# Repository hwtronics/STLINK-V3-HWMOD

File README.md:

# STLINK-V3-HWMOD

Custom developed board that allow you to use the new STLINK-V3MODS with the Tag-Connect cable.

## Preview of the board:

## Prerequisite
Autodesk Eagle

## Social Media Links

Instagram: [@hwtronics](https://www.instagram.com/hwtronics/)
Facebook: [@hwtronics](https://www.facebook.com/hwtronics/)
Twitter: [@hwtronics](https://twitter.com/hwtronics)

Distributed under the GNU General Public License v3.0 license. See ``LICENSE`` for more information.

For any further info please contact us by email: info@hwtronics.com !!!

## Contributors

-[@dinamitemic](https://github.com/dinamitemic)
-[@AnnaBiguzzi](https://github.com/AnnaBiguzzi)

## Contributing

1. Fork it (<https://github.com/yourname/yourproject/fork>)
2. Create your feature branch (`git checkout -b feature/fooBar`)
3. Commit your changes (`git commit -am 'Add some fooBar'`)
4. Push to the branch (`git push origin feature/fooBar`)
5. Create a new Pull Request

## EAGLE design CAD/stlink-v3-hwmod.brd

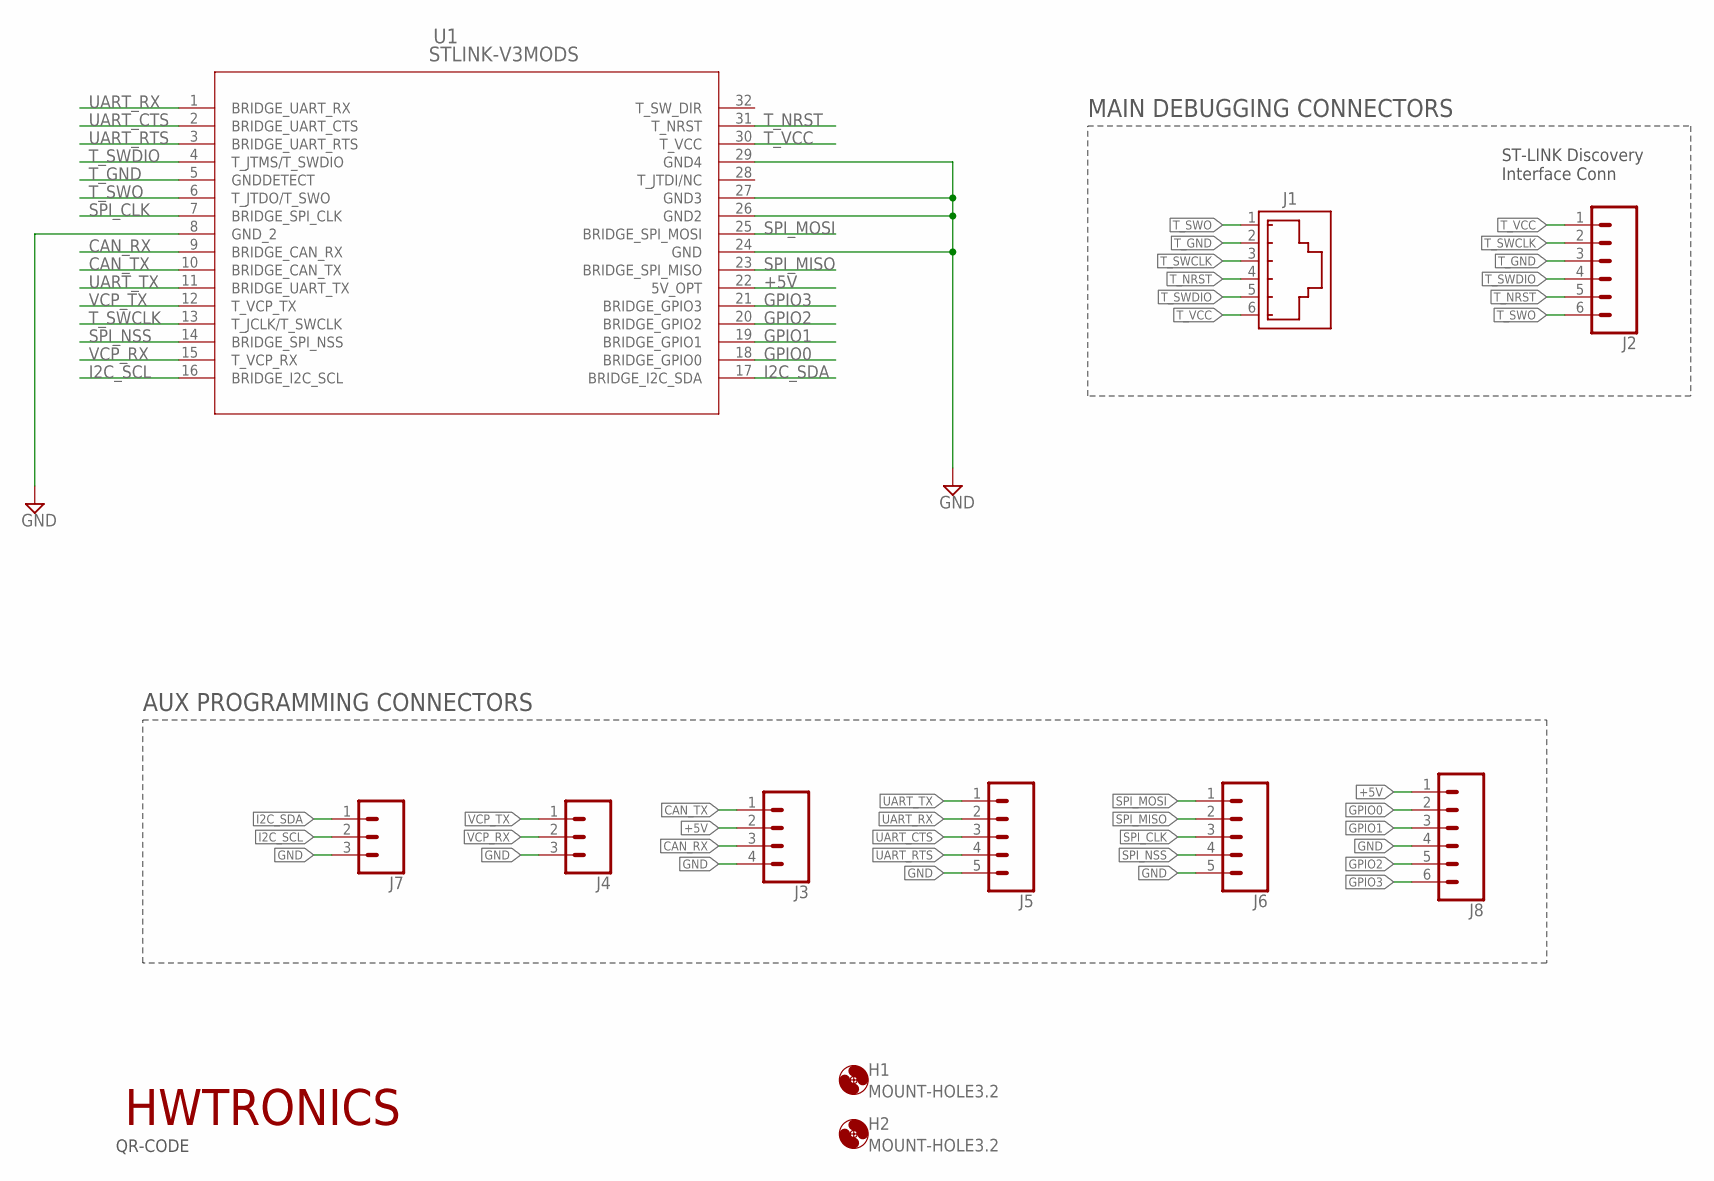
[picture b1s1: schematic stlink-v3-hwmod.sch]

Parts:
H1, H2: MOUNT-HOLE3.2; 3,2
J1: 615006143621
J2, J8: CONN_06SILK_FEMALE_PTH; 1X06
J3: CONN_04; 1X04
J4, J7: CONN_03; 1X03
J5, J6: CONN_05; 1X05
LOGO1: LOGO-HWTRONICS-10MM; HWTRONICS-10MM
U1: STLINK-V3MODS; MOD_STLINK-V3M_MB1467
U$1: STLINK-V3-HWMODS

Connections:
+5V: J3.2, J8.1, U1.22 (5V_OPT)
CAN_RX: J3.3, U1.9 (BRIDGE_CAN_RX)
CAN_TX: J3.1, U1.10 (BRIDGE_CAN_TX)
GND: J3.4, J4.3, J5.5, J6.5, J7.3, J8.4, U1.8 (GND_2), U1.24 (GND), U1.26 (GND2), U1.27 (GND3), U1.29 (GND4)
GPIO0: J8.2, U1.18 (BRIDGE_GPIO0)
GPIO1: J8.3, U1.19 (BRIDGE_GPIO1)
GPIO2: J8.5, U1.20 (BRIDGE_GPIO2)
GPIO3: J8.6, U1.21 (BRIDGE_GPIO3)
I2C_SCL: J7.2, U1.16 (BRIDGE_I2C_SCL)
I2C_SDA: J7.1, U1.17 (BRIDGE_I2C_SDA)
SPI_CLK: J6.3, U1.7 (BRIDGE_SPI_CLK)
SPI_MISO: J6.2, U1.23 (BRIDGE_SPI_MISO)
SPI_MOSI: J6.1, U1.25 (BRIDGE_SPI_MOSI)
SPI_NSS: J6.4, U1.14 (BRIDGE_SPI_NSS)
T_GND: J1.2 (5), J2.3, U1.5 (GNDDETECT)
T_NRST: J1.4 (3), J2.5, U1.31 (T_NRST)
T_SWCLK: J1.3 (4), J2.2, U1.13 (T_JCLK/T_SWCLK)
T_SWDIO: J1.5 (2), J2.4, U1.4 (T_JTMS/T_SWDIO)
T_SWO: J1.1 (6), J2.6, U1.6 (T_JTDO/T_SWO)
T_VCC: J1.6 (1), J2.1, U1.30 (T_VCC)
UART_CTS: J5.3, U1.2 (BRIDGE_UART_CTS)
UART_RTS: J5.4, U1.3 (BRIDGE_UART_RTS)
UART_RX: J5.2, U1.1 (BRIDGE_UART_RX)
UART_TX: J5.1, U1.11 (BRIDGE_UART_TX)
VCP_RX: J4.2, U1.15 (T_VCP_RX)
VCP_TX: J4.1, U1.12 (T_VCP_TX)

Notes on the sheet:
ST-LINK Discovery Interface Conn
MAIN DEBUGGING CONNECTORS
AUX PROGRAMMING CONNECTORS

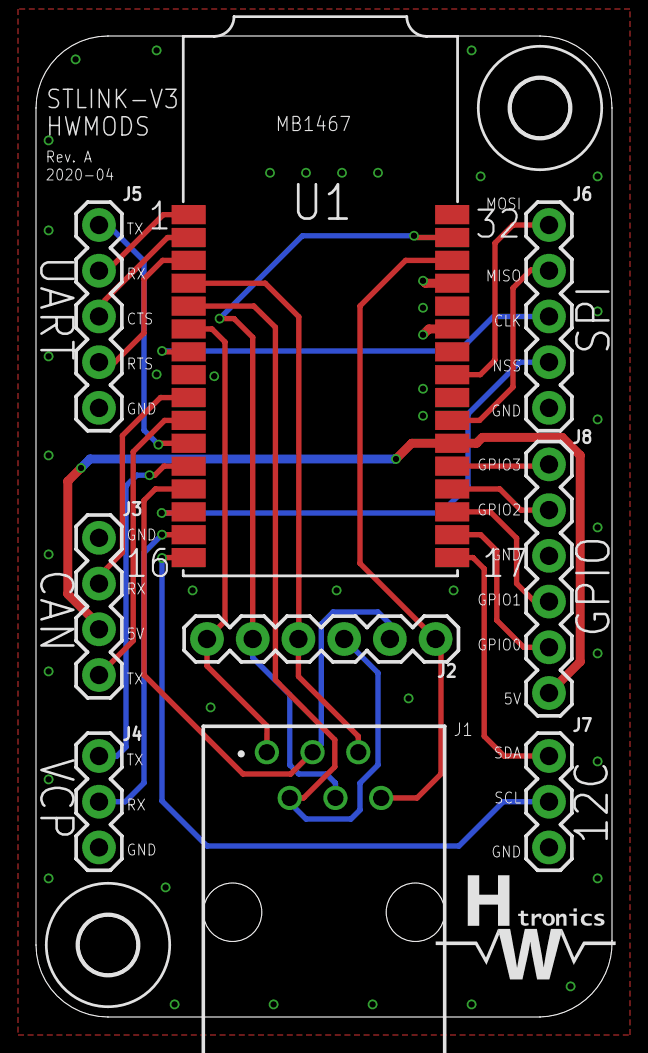
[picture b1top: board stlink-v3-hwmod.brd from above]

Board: 2 copper layers, 32.0 x 54.5 mm, 13 parts (1 on the bottom side), 26 nets.

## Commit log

2020-03-13 First version of cad done!
2020-04-03 Final revision.
    Created Gerbers,
    Ready for production
2020-04-03 Rendering updates
2020-04-03 images update
2020-04-03 images update 2
2020-08-20 Non so cosa sia ma mi da danno che ci sia la spunta rossa

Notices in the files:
parts and their libraries:
615002138421_Eagle_WR-MJ_rev20a: Copyright: Würth Elektronik
SparkFun-Connectors: Licensing: Creative Commons ShareAlike 4.0 International - https://creativecommons.org/licenses/by-sa/4.0
